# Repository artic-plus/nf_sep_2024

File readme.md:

# nf_sep_2024

*A short description of the keyboard/project*

* Keyboard Maintainer: [artic-plus](https://github.com/artic-plus)
* Hardware Supported: *The PCBs, controllers supported*
* Hardware Availability: *Links to where you can find this hardware*

Make example for this keyboard (after setting up your build environment):

    make nf_sep_2024:default

Flashing example for this keyboard:

    make nf_sep_2024:default:flash

See the [build environment setup](https://docs.qmk.fm/#/getting_started_build_tools) and the [make instructions](https://docs.qmk.fm/#/getting_started_make_guide) for more information. Brand new to QMK? Start with our [Complete Newbs Guide](https://docs.qmk.fm/#/newbs).

## Bootloader

Enter the bootloader in 3 ways:

* **Bootmagic reset**: Hold down the key at (0,0) in the matrix (usually the top left key or Escape) and plug in the keyboard
* **Physical reset button**: Briefly press the button on the back of the PCB - some may have pads you must short instead
* **Keycode in layout**: Press the key mapped to `QK_BOOT` if it is available

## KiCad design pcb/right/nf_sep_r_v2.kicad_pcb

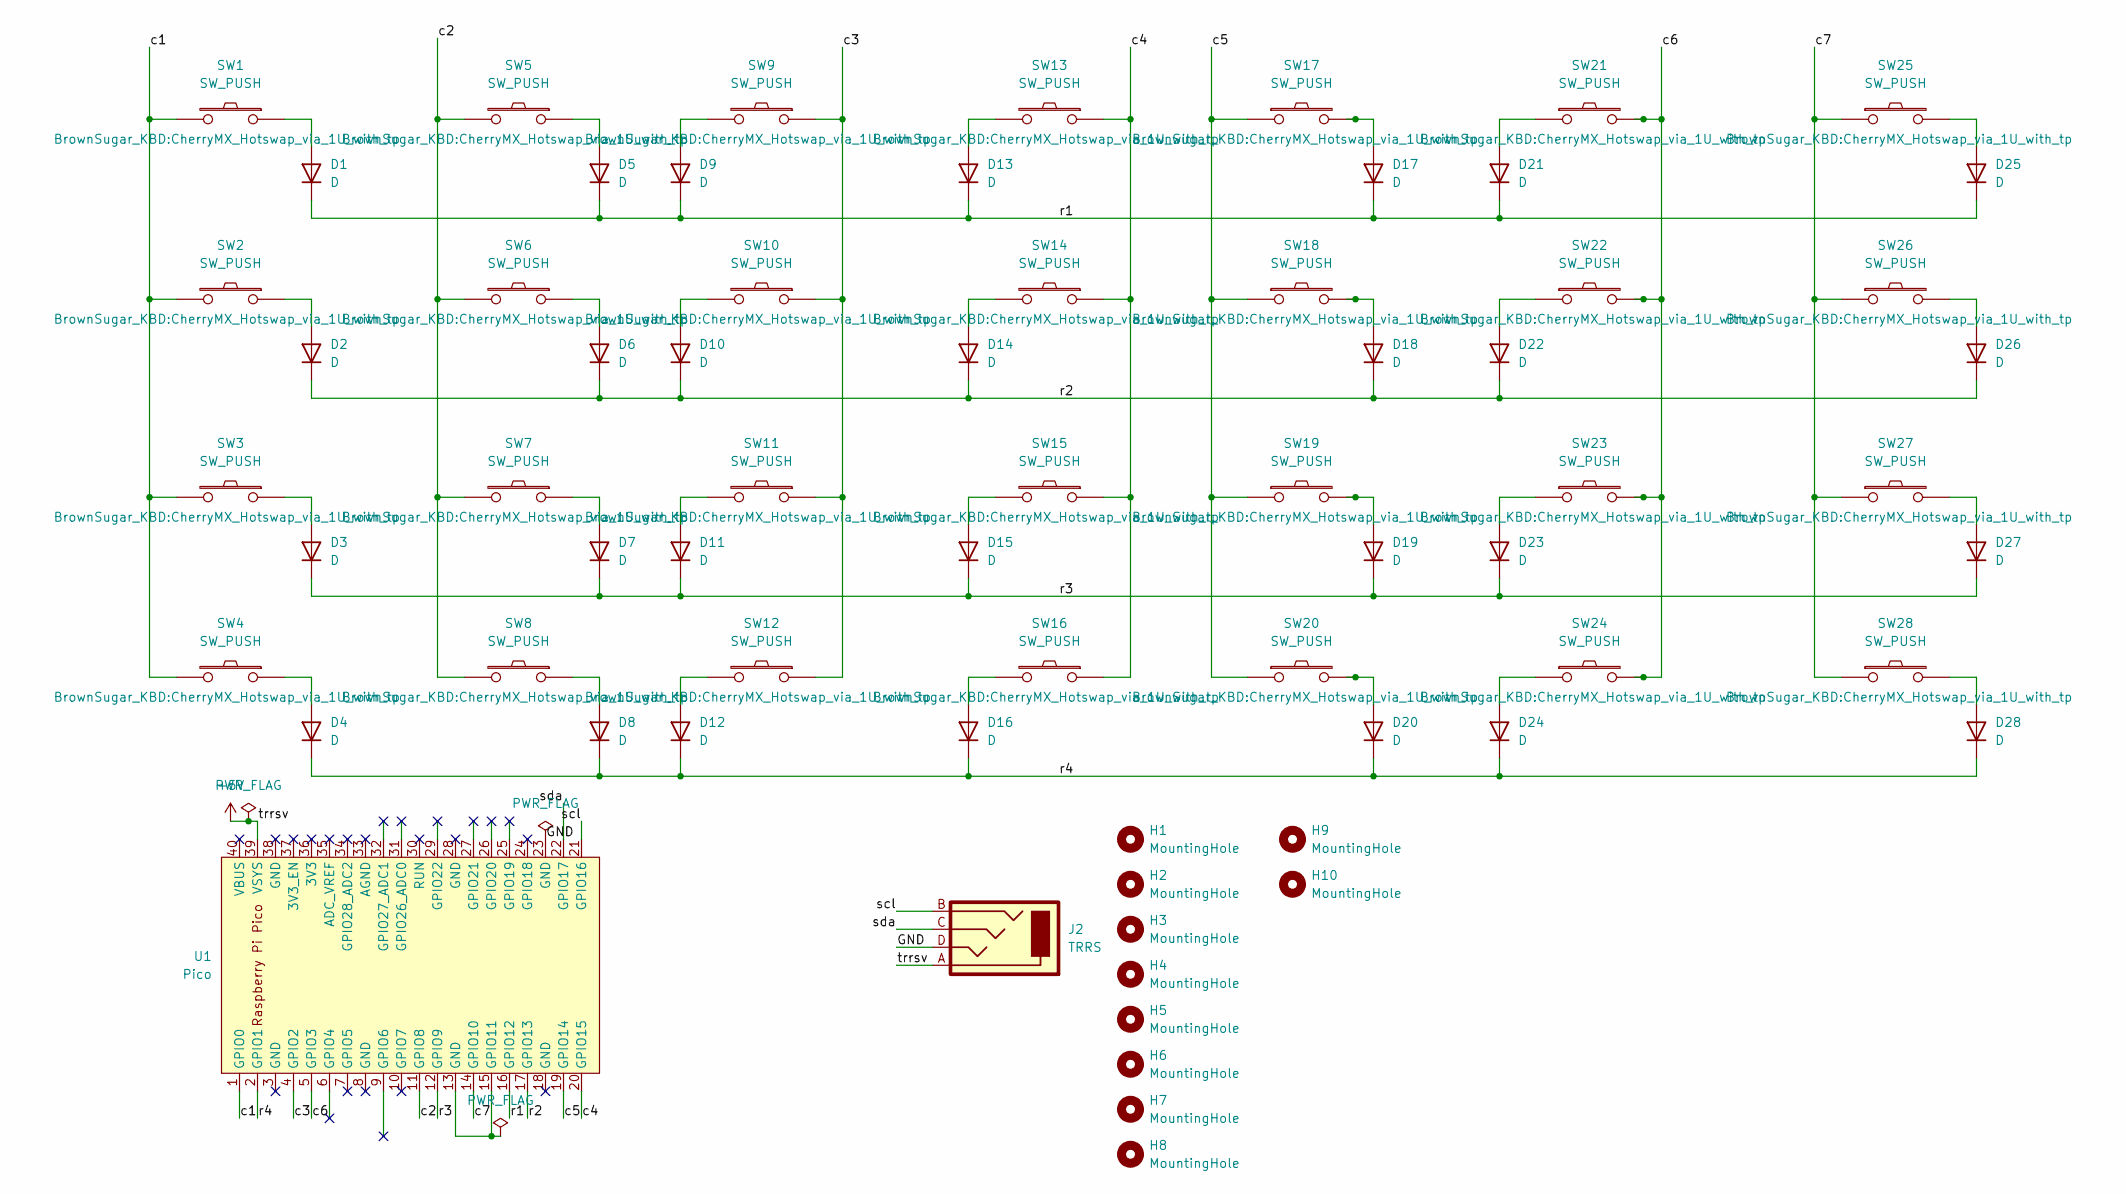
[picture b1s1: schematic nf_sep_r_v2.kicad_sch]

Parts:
D1, D3, D14, D16, D17, D18, D19, D20, D25, D26, D27, D28: D; D_DO-34_SOD68_P12.70mm_Horizontal
D2, D4, D13, D15: D; D_DO-15_P15.24mm_Horizontal
D5, D7, D10, D12, D22, D24: D; D_DO-34_SOD68_P7.62mm_Horizontal
D6, D8, D9, D11, D21, D23: D; D_DO-34_SOD68_P10.16mm_Horizontal
H1, H2, H3, H4, H5, H6, H7, H8, H9, H10: MountingHole; mountinghole_M2
J2: TRRS; TRRS_PJ-320A
SW1, SW2, SW3, SW4, SW5, SW6, SW7, SW8, SW9, SW10, SW11, SW12, SW13, SW14, SW15, SW16, SW17, SW18, SW19, SW20, SW21, SW22, SW23, SW24, SW25, SW26, SW27, SW28: SW_PUSH; CherryMX_Hotswap_via_1U_with_tp
U1: Pico; RPi_Pico_SMD_TH_NO_DEBUG

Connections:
+5V: J2.A, U1.39 (VSYS)
/GND: J2.D, U1.23 (GND)
/c1: SW1.2, SW2.2, SW3.2, SW4.2, U1.1 (GPIO0)
/c2: SW5.2, SW6.2, SW7.2, SW8.2, U1.11 (GPIO8)
/c3: SW9.1, SW10.1, SW11.1, SW12.1, U1.4 (GPIO2)
/c4: SW13.1, SW14.1, SW15.1, SW16.1, U1.20 (GPIO15)
/c5: SW17.1, SW18.1, SW19.1, SW20.1, U1.19 (GPIO14)
/c6: SW21.2, SW22.2, SW23.2, SW24.2, U1.5 (GPIO3)
/c7: SW25.1, SW26.1, SW27.1, SW28.1, U1.14 (GPIO10)
/r1: D1.1 (K), D5.1 (K), D9.1 (K), D13.1 (K), D17.1 (K), D21.1 (K), D25.1 (K), U1.16 (GPIO12)
/r2: D2.1 (K), D6.1 (K), D10.1 (K), D14.1 (K), D18.1 (K), D22.1 (K), D26.1 (K), U1.17 (GPIO13)
/r3: D3.1 (K), D7.1 (K), D11.1 (K), D15.1 (K), D19.1 (K), D23.1 (K), D27.1 (K), U1.12 (GPIO9)
/r4: D4.1 (K), D8.1 (K), D12.1 (K), D16.1 (K), D20.1 (K), D24.1 (K), D28.1 (K), U1.2 (GPIO1)
/scl: J2.B, U1.21 (GPIO16)
/sda: J2.C, U1.22 (GPIO17)
unnamed: D1.2 (A), SW1.1
unnamed: D2.2 (A), SW2.1
unnamed: D3.2 (A), SW3.1
unnamed: D4.2 (A), SW4.1
unnamed: D5.2 (A), SW5.1
unnamed: D6.2 (A), SW6.1
unnamed: D7.2 (A), SW7.1
unnamed: D8.2 (A), SW8.1
unnamed: D9.2 (A), SW9.2
unnamed: D10.2 (A), SW10.2
unnamed: D11.2 (A), SW11.2
unnamed: D12.2 (A), SW12.2
unnamed: D13.2 (A), SW13.2
unnamed: D14.2 (A), SW14.2
unnamed: D15.2 (A), SW15.2
unnamed: D16.2 (A), SW16.2
unnamed: D17.2 (A), SW17.2
unnamed: D18.2 (A), SW18.2
unnamed: D19.2 (A), SW19.2
unnamed: D20.2 (A), SW20.2
unnamed: D21.2 (A), SW21.1
unnamed: D22.2 (A), SW22.1
unnamed: D23.2 (A), SW23.1
unnamed: D24.2 (A), SW24.1
unnamed: D25.2 (A), SW25.2
unnamed: D26.2 (A), SW26.2
unnamed: D27.2 (A), SW27.2
unnamed: D28.2 (A), SW28.2
unnamed: U1.13 (GND), U1.15 (GPIO11)

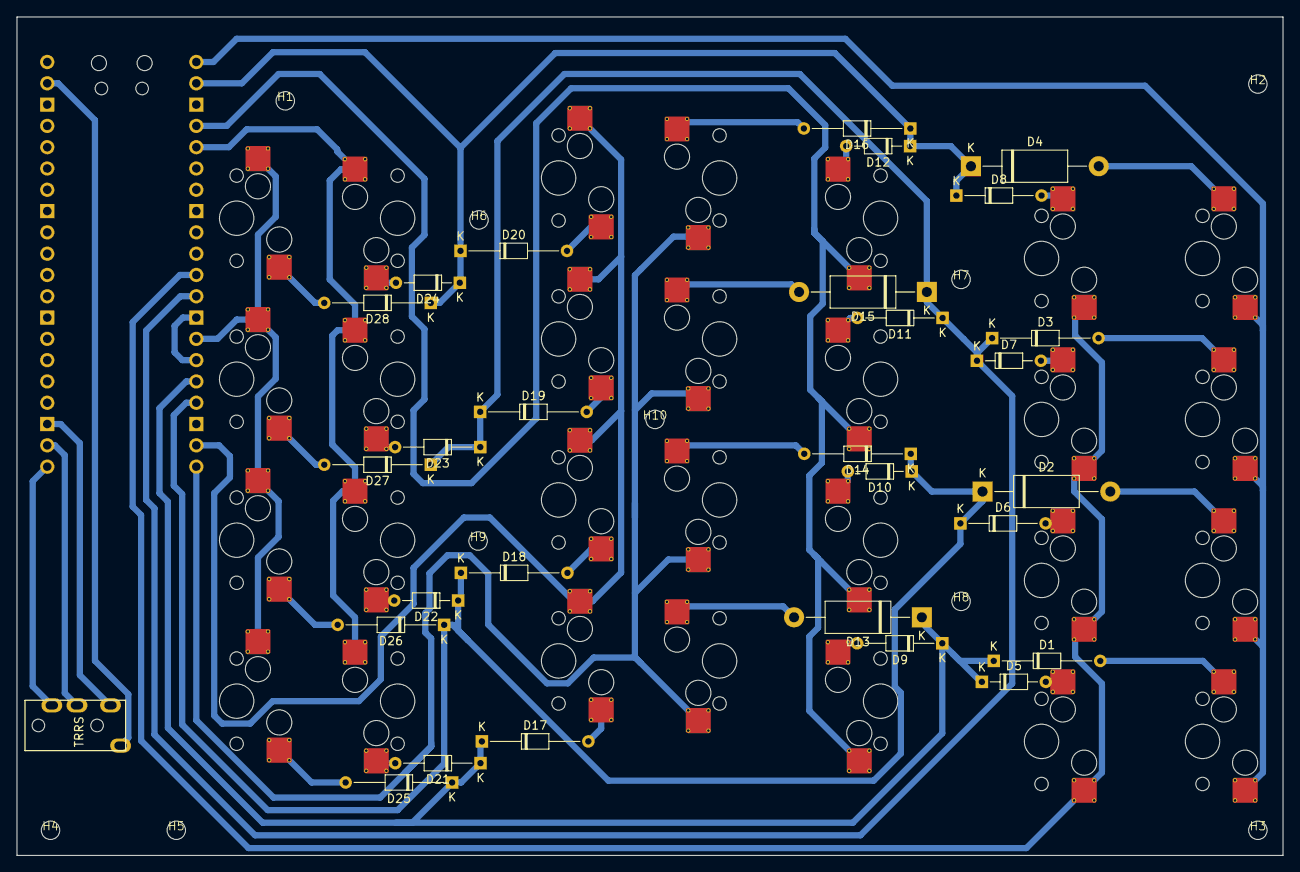
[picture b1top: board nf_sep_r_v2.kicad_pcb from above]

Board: 2 copper layers, 151.0 x 100.0 mm, 68 parts (1 on the bottom side), 44 nets.

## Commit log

2024-11-22 add pcb data
2024-11-27 remap support
